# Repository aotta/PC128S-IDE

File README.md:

# PC128S-IDE
An IDE interface for Olivetti Prodest PC128S & Master Compact
Further info on stardot.org.uk
Some note for soldering:
the Edge pin 10 doesn't need to be connected, it was for experimenting 1 mhz port, but it didn't work with ide drive. So, you can solder a link for 2mhz in j4 between pin 2 and 3, and avoid the jumper.
Note it's needed the 74HCxx series, not the 74LSxx one.
Remind to solder the connector edge slot in the right way (soldering from component side, not the solder side!)

Feel free to improve or change the boards, and my credits to J.G. Harston for original schemes ( https://mdfs.net/Info/Comp/BBC/IDE/ )

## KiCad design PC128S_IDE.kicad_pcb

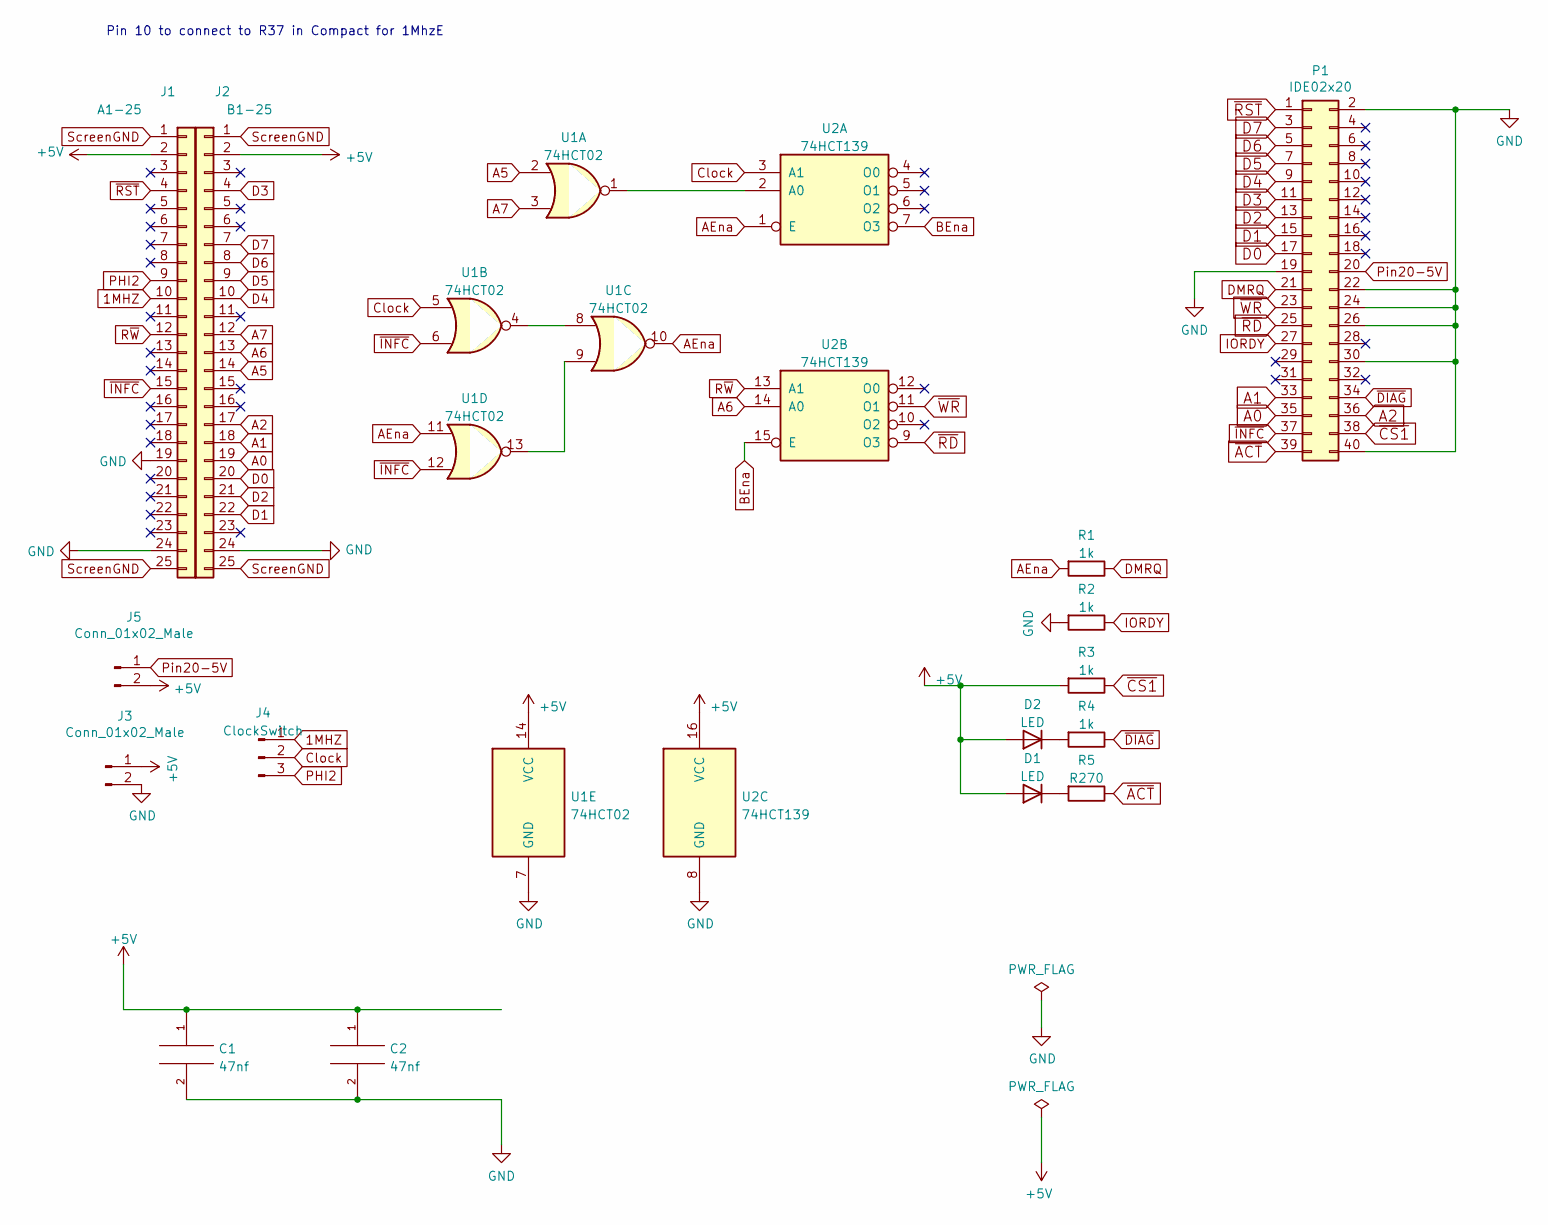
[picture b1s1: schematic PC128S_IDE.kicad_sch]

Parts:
C1, C2: 47nf; C_Disc_D4.7mm_W2.5mm_P5.00mm
D1, D2: LED; LED_D3.0mm
J1: A1-25; PinHeader_1x25_P2.54mm_Vertical
J2: B1-25; PinHeader_1x25_P2.54mm_Vertical
J3, J5: Conn_01x02_Male; PinSocket_1x02_P2.54mm_Vertical
J4: ClockSwitch; PinHeader_1x03_P2.54mm_Vertical
P1: IDE02x20; PinHeader_2x20_P2.54mm_Vertical
R1, R2, R3, R4: 1k; R_Axial_DIN0207_L6.3mm_D2.5mm_P7.62mm_Horizontal
R5: R270; R_Axial_DIN0207_L6.3mm_D2.5mm_P7.62mm_Horizontal
U1: 74HCT02; DIP-14_W7.62mm
U2: 74HCT139; DIP-16_W7.62mm

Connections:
1MHZ: J1.10, J4.1
+5V: C1.1, C2.1, D1.2 (A), D2.2 (A), J1.2, J2.2, J3.1, J5.2, R3.2, U1.14 (VCC), U2.16 (VCC)
A0: J2.19, P1.35
A1: J2.18, P1.33
A2: J2.17, P1.36
A5: J2.14, U1.2
A6: J2.13, U2.14 (A0)
A7: J2.12, U1.3
AEna: R1.2, U1.10, U1.11, U2.1 (E)
BEna: U2.7 (O3), U2.15 (E)
Clock: J4.2, U1.5, U2.3 (A1)
D0: J2.20, P1.17
D1: J2.22, P1.15
D2: J2.21, P1.13
D3: J2.4, P1.11
D4: J2.10, P1.9
D5: J2.9, P1.7
D6: J2.8, P1.5
D7: J2.7, P1.3
DMRQ: P1.21, R1.1
GND: C1.2, C2.2, J1.19, J1.24, J2.24, J3.2, P1.2, P1.19, P1.22, P1.24, P1.26, P1.30, P1.40, R2.2, U1.7 (GND), U2.8 (GND)
IORDY: P1.27, R2.1
unnamed: D1.1 (K), R5.2
unnamed: D2.1 (K), R4.2
unnamed: U1.1, U2.2 (A0)
unnamed: U1.4, U1.8
unnamed: U1.9, U1.13
PHI2: J1.9, J4.3
Pin20-5V: J5.1, P1.20
R~W: J1.12, U2.13 (A1)
ScreenGND: J1.1, J1.25, J2.1, J2.25
~ACT: P1.39, R5.1
~CS1: P1.38, R3.1
~DIAG: P1.34, R4.1
~INFC: J1.15, P1.37, U1.6, U1.12
~RD: P1.25, U2.9 (O3)
~RST: J1.4, P1.1
~WR: P1.23, U2.11 (O1)

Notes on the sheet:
Pin 10 to connect to R37 in Compact for 1MhzE

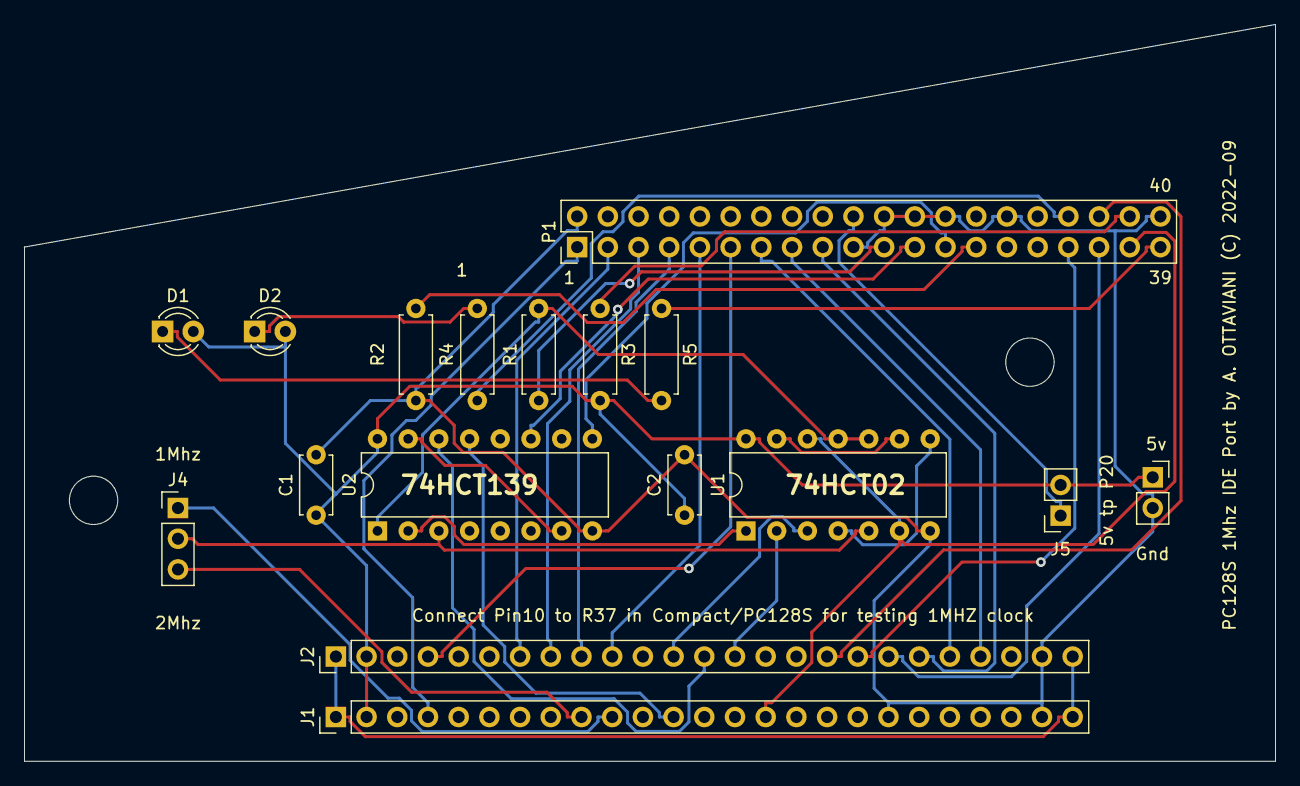
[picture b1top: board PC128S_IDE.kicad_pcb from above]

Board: 2 copper layers, 103.5 x 61.0 mm, 17 parts (0 on the bottom side), 38 nets.

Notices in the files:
PC128S_IDE.kicad_pcb:
PC128S 1Mhz IDE Port by A. OTTAVIANI (C) 2022-09
